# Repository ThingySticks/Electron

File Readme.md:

Electron Prototyping PCB.
=======================

Prototype board for Particle Electron.

See individual versions for PCB specifics.

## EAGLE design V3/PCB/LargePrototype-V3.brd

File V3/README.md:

Electron Prototype PCB.

Designed to fit Takachi WP11-15-4C case (150 x 110 x 40mm)

Farnell: 2472097

[Available on Tindie](https://www.tindie.com/products/ThingySticks/photonelectron-prototyping-pcb-for-ip67-enclosure/)

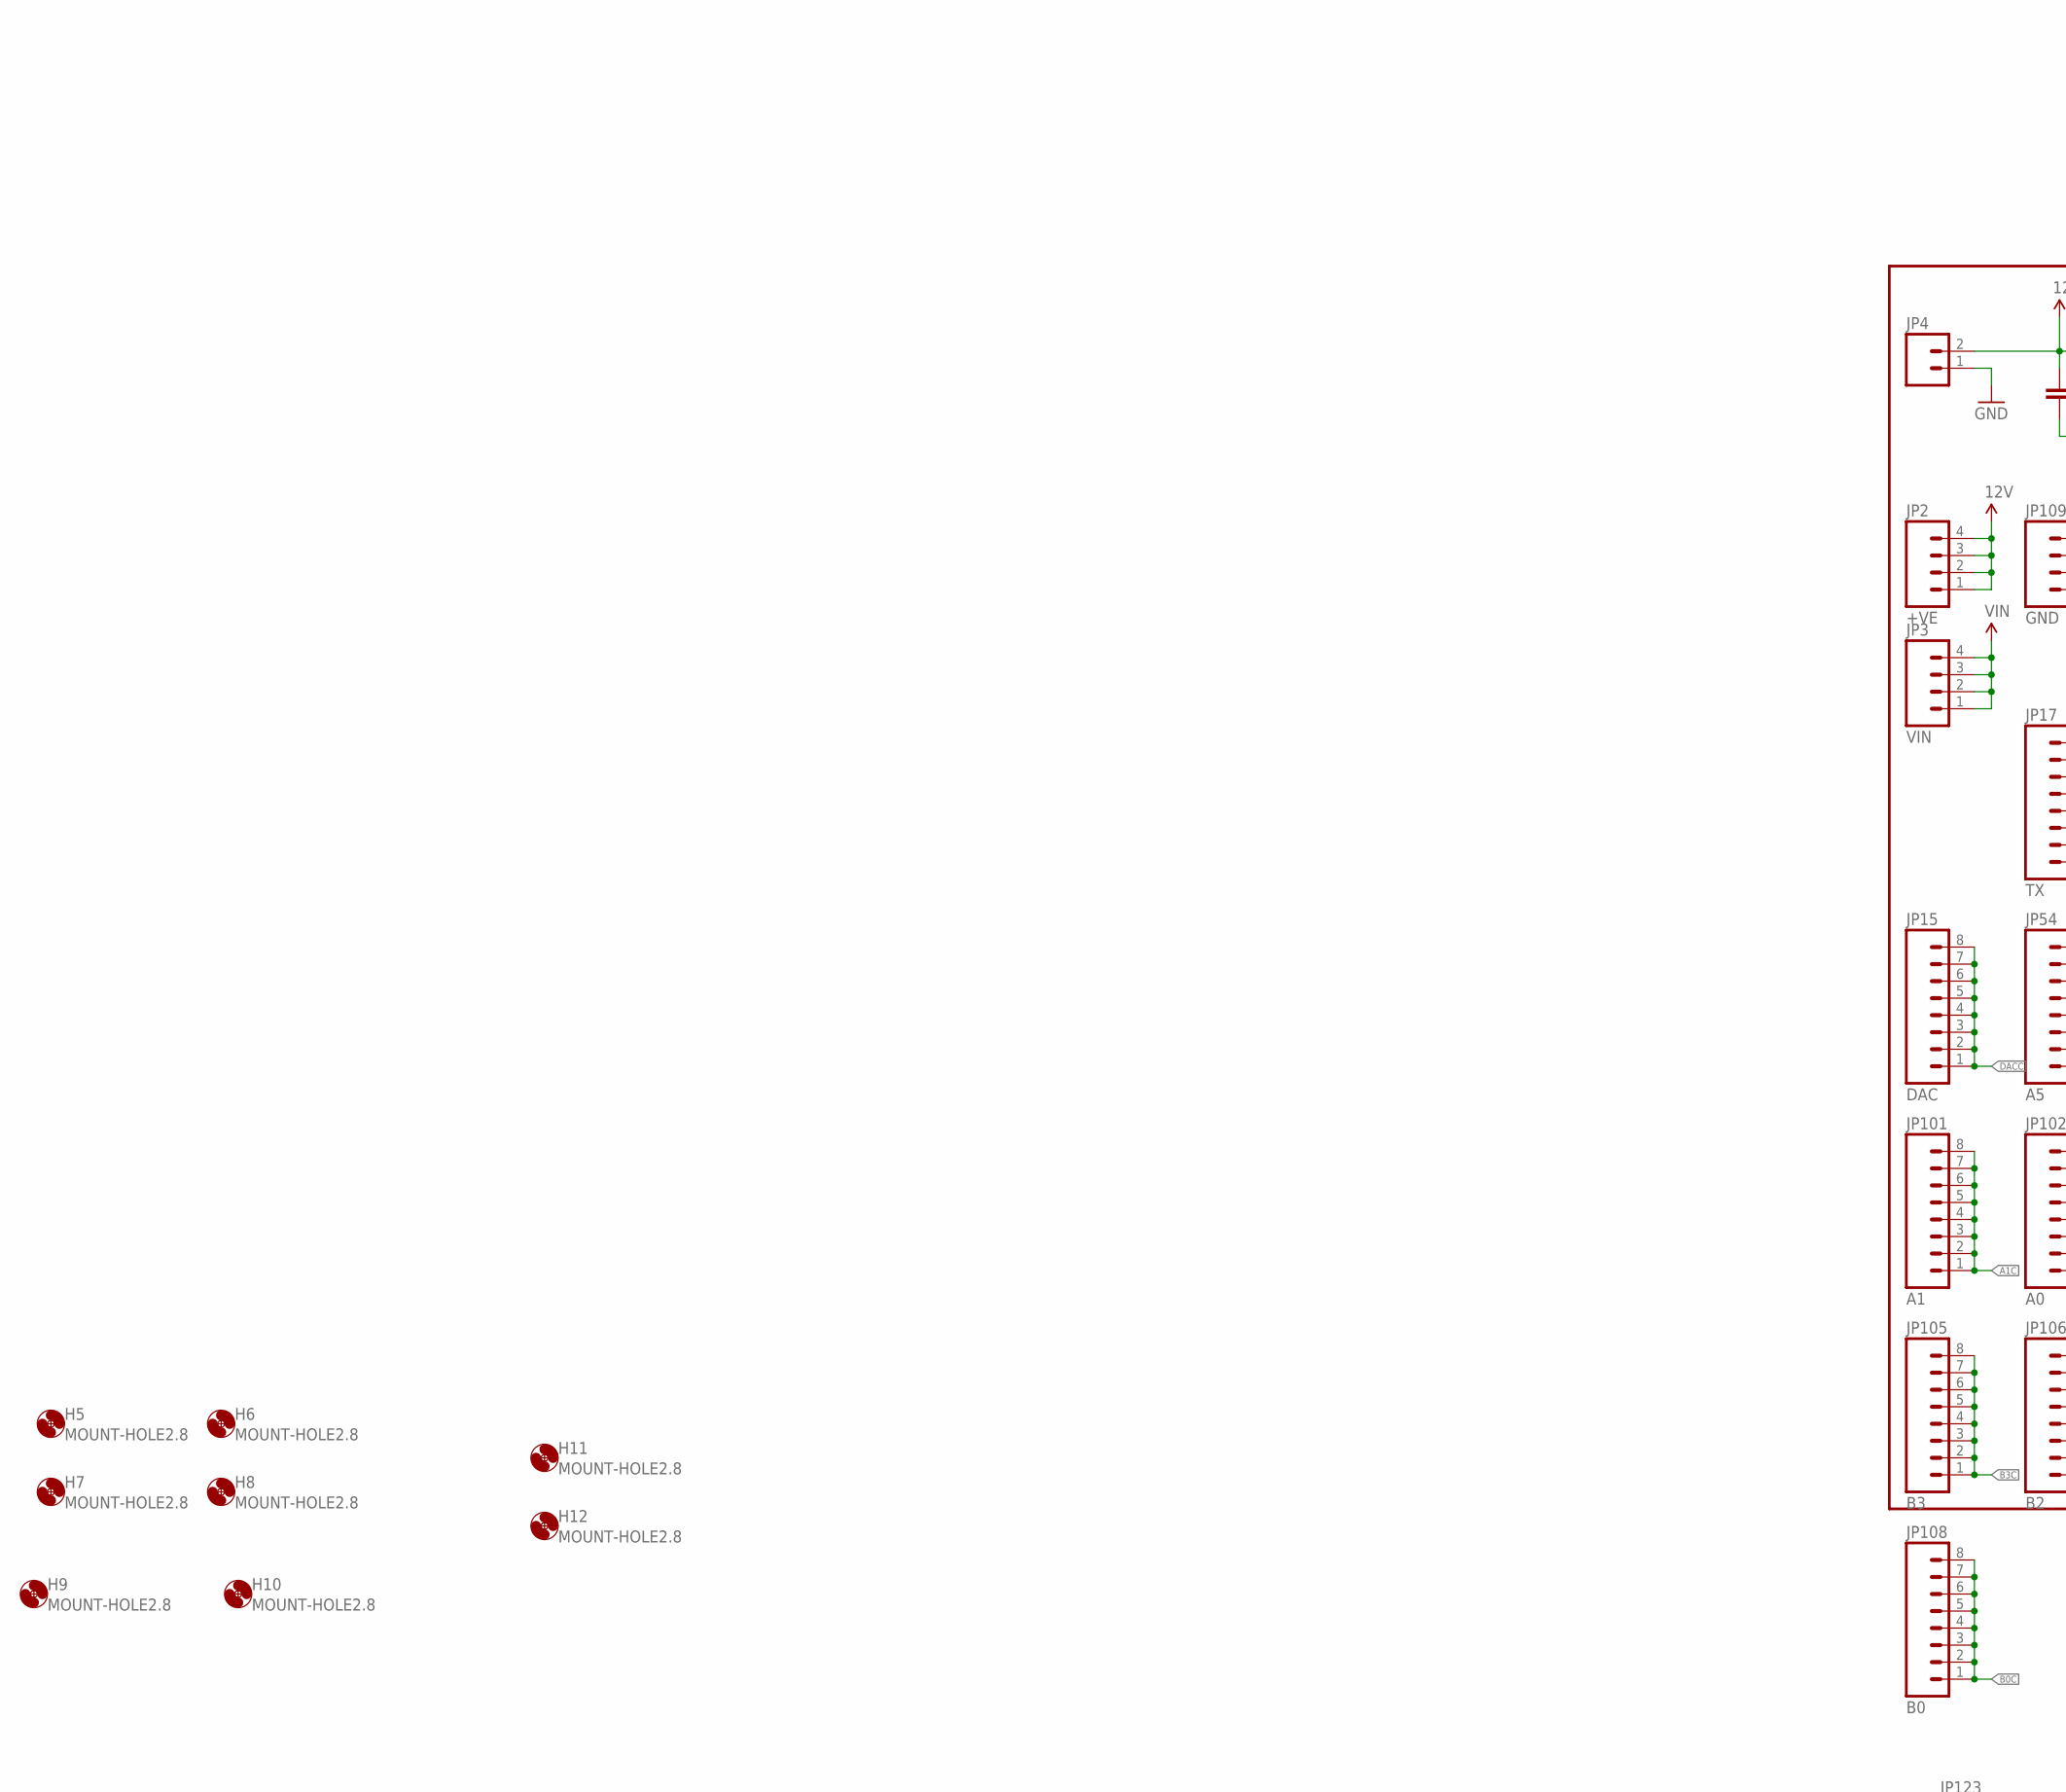
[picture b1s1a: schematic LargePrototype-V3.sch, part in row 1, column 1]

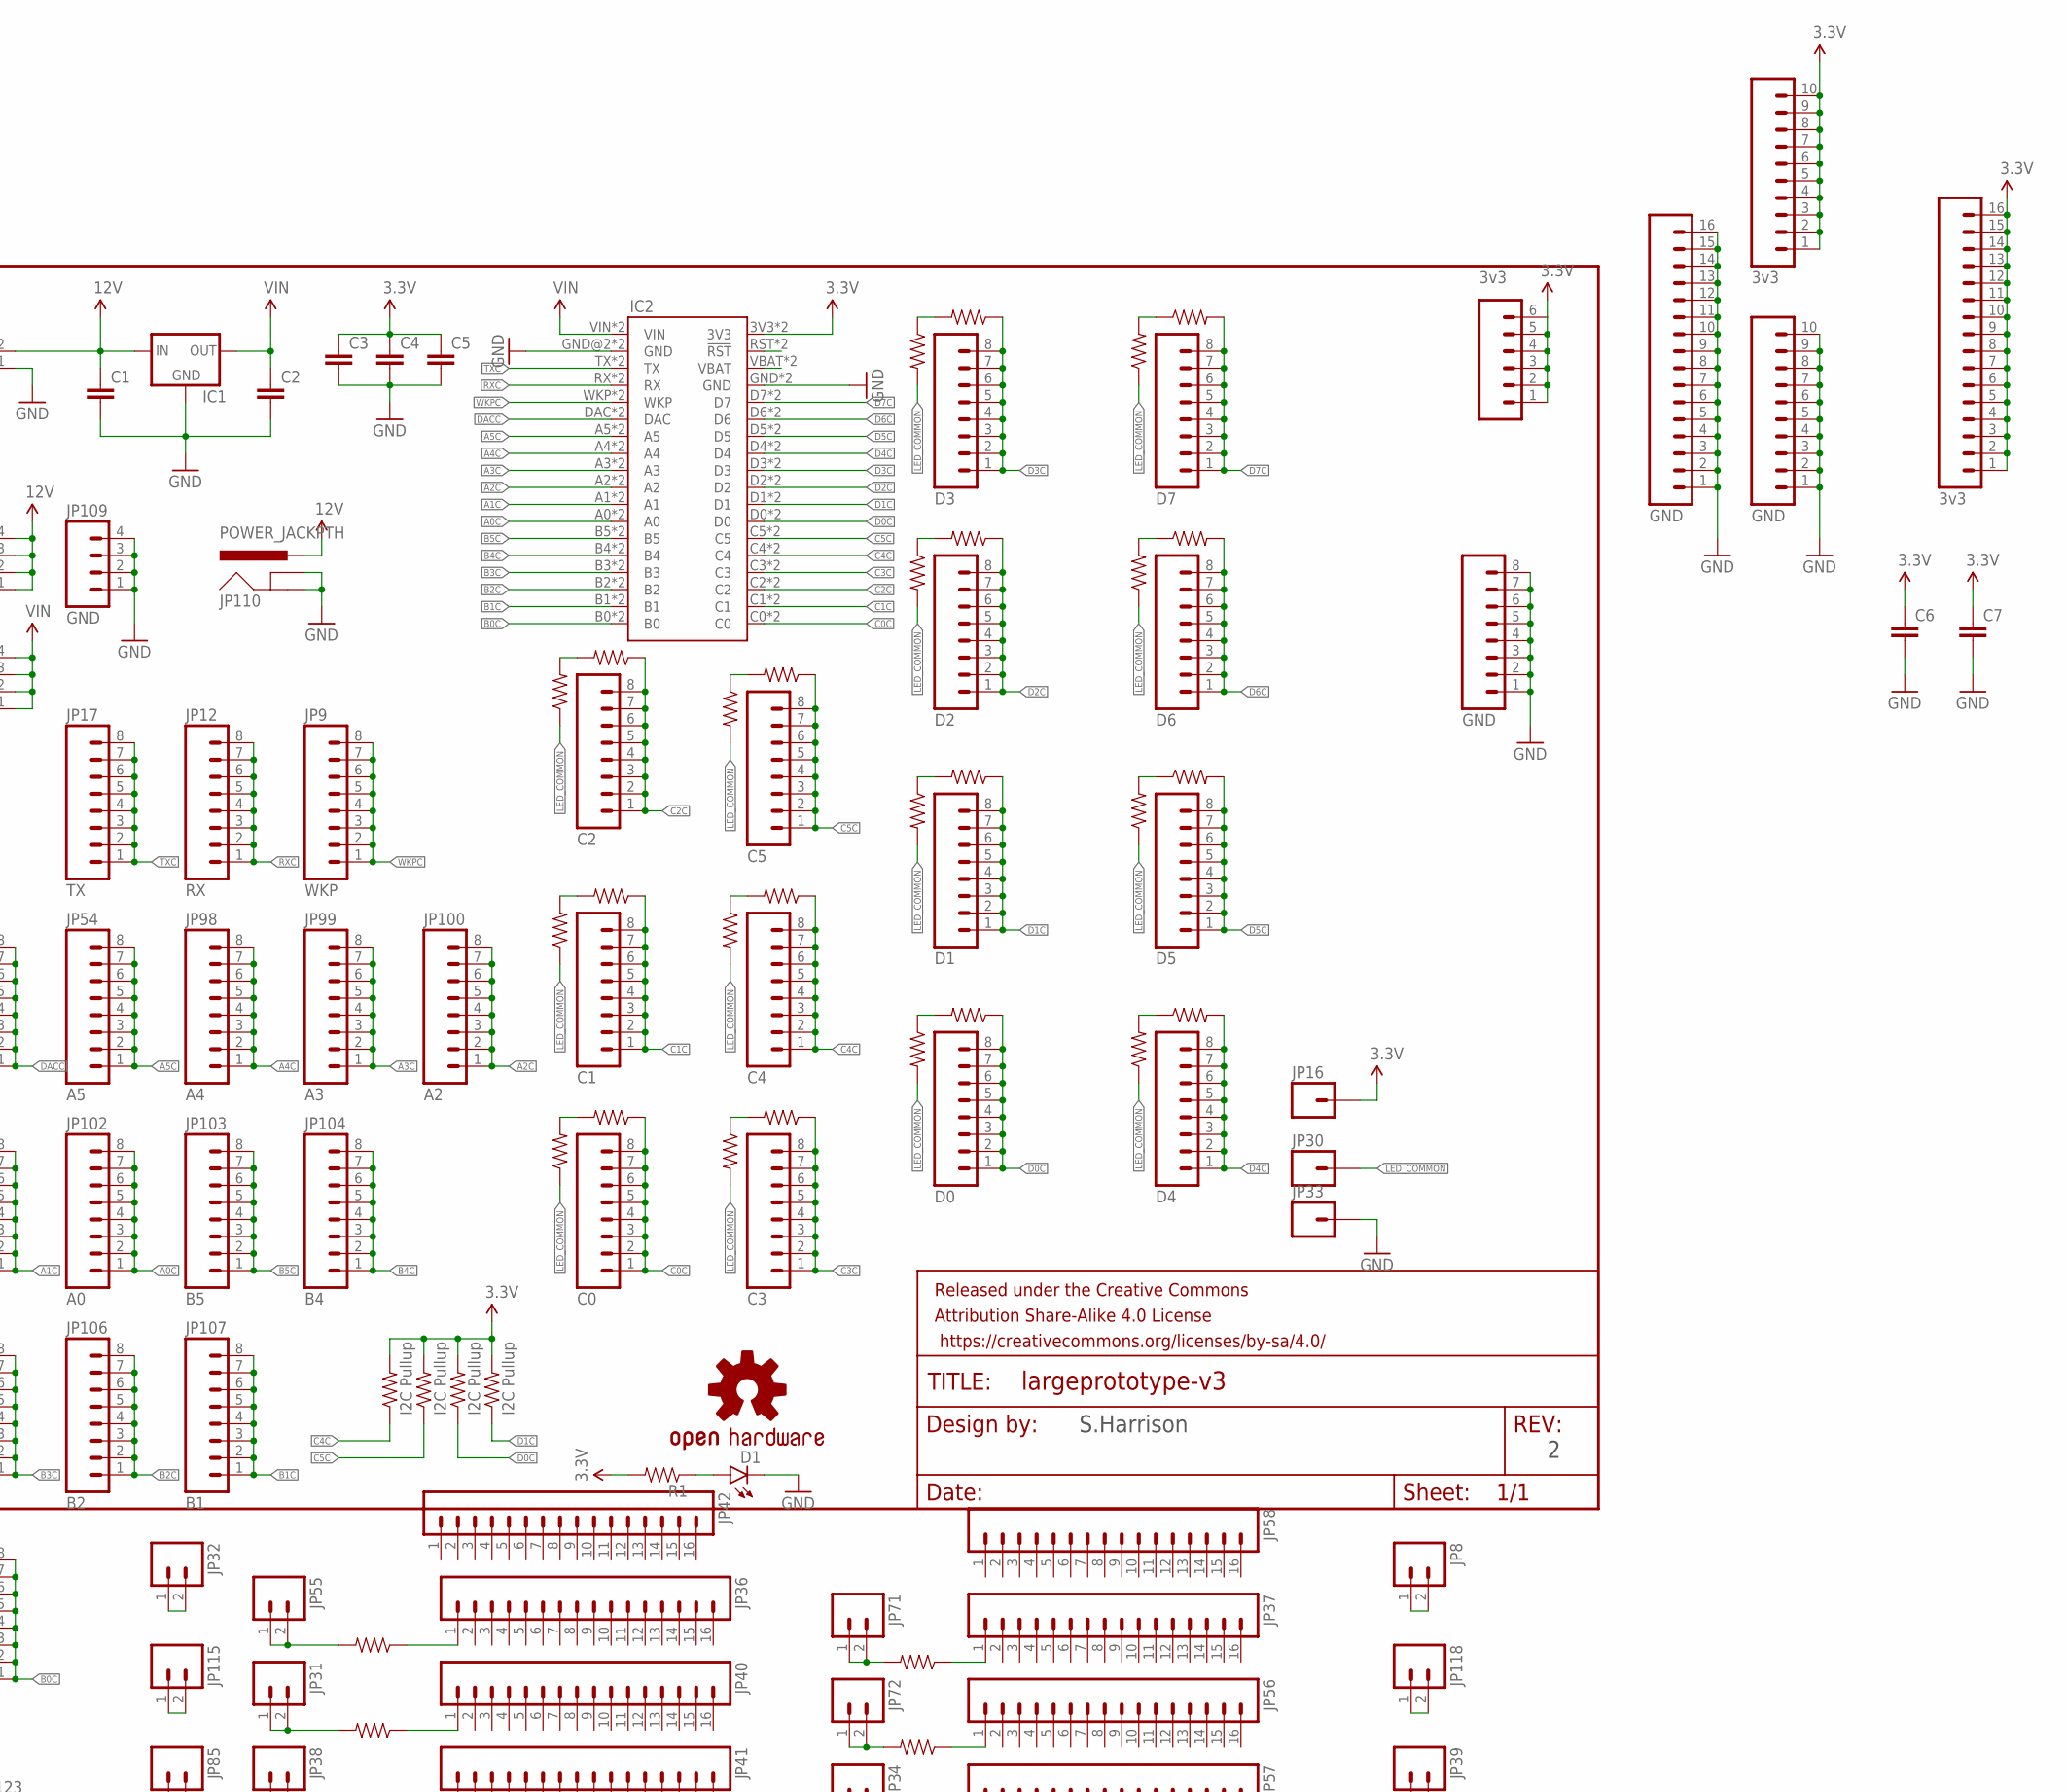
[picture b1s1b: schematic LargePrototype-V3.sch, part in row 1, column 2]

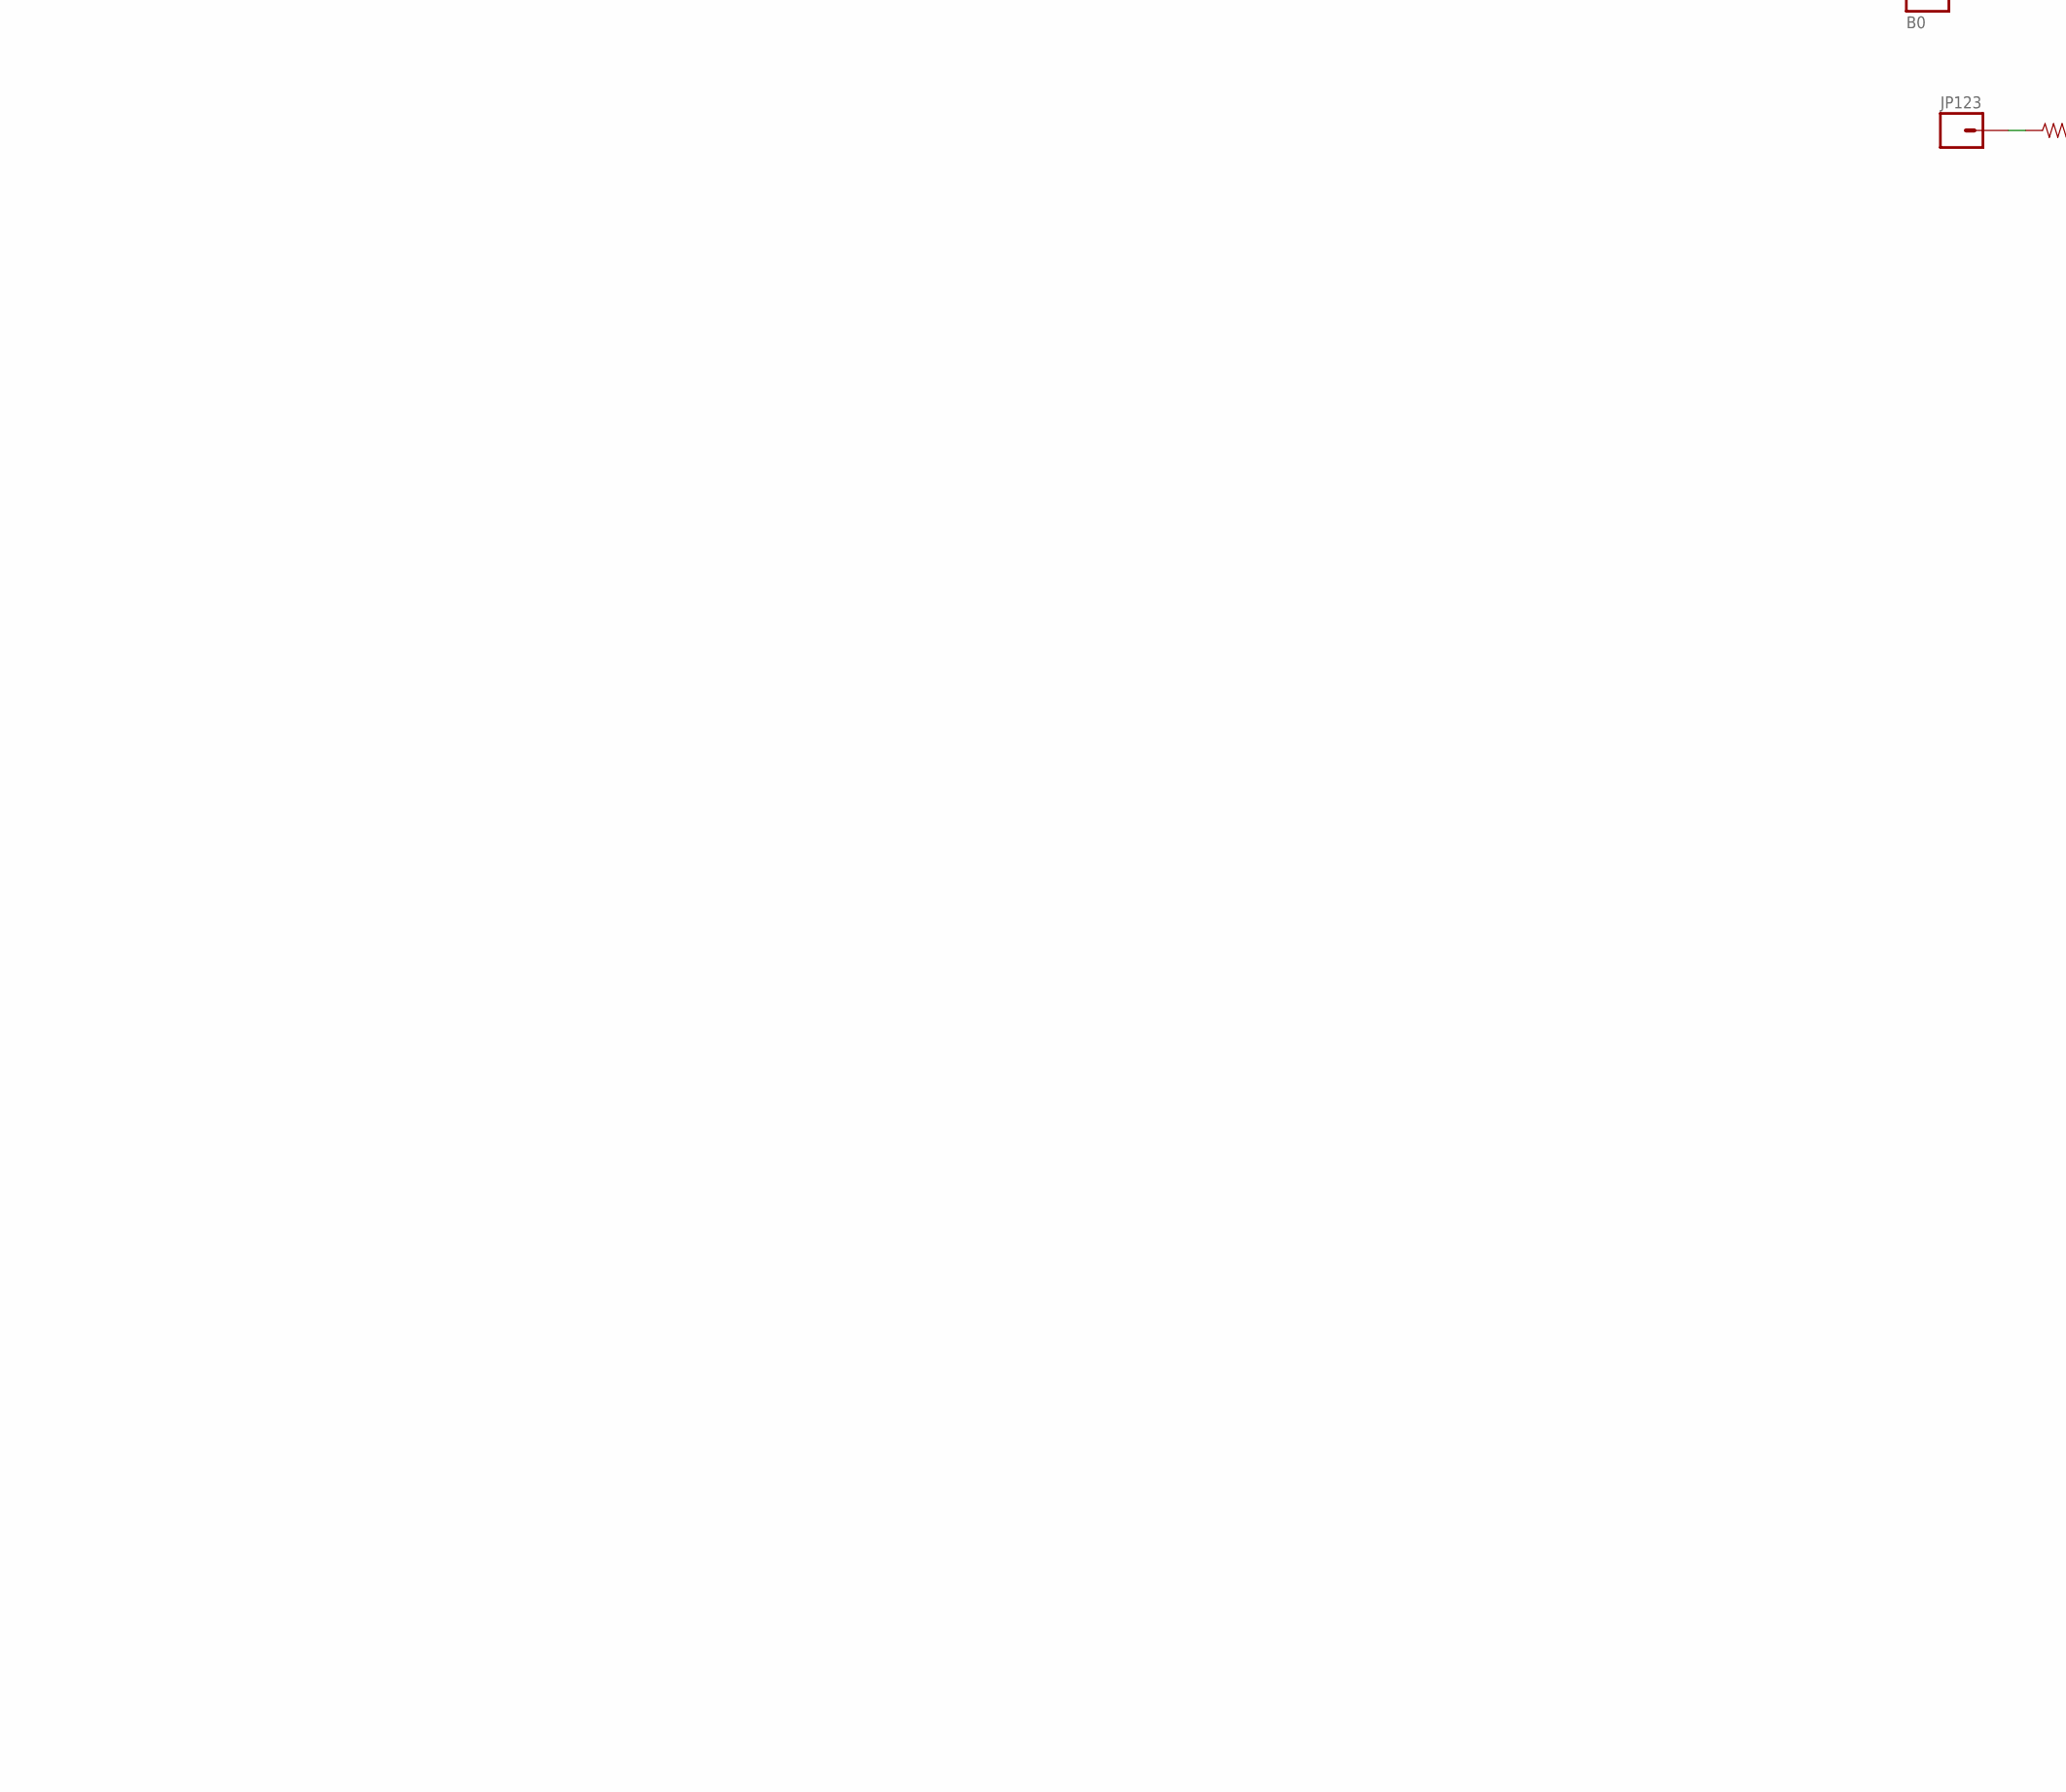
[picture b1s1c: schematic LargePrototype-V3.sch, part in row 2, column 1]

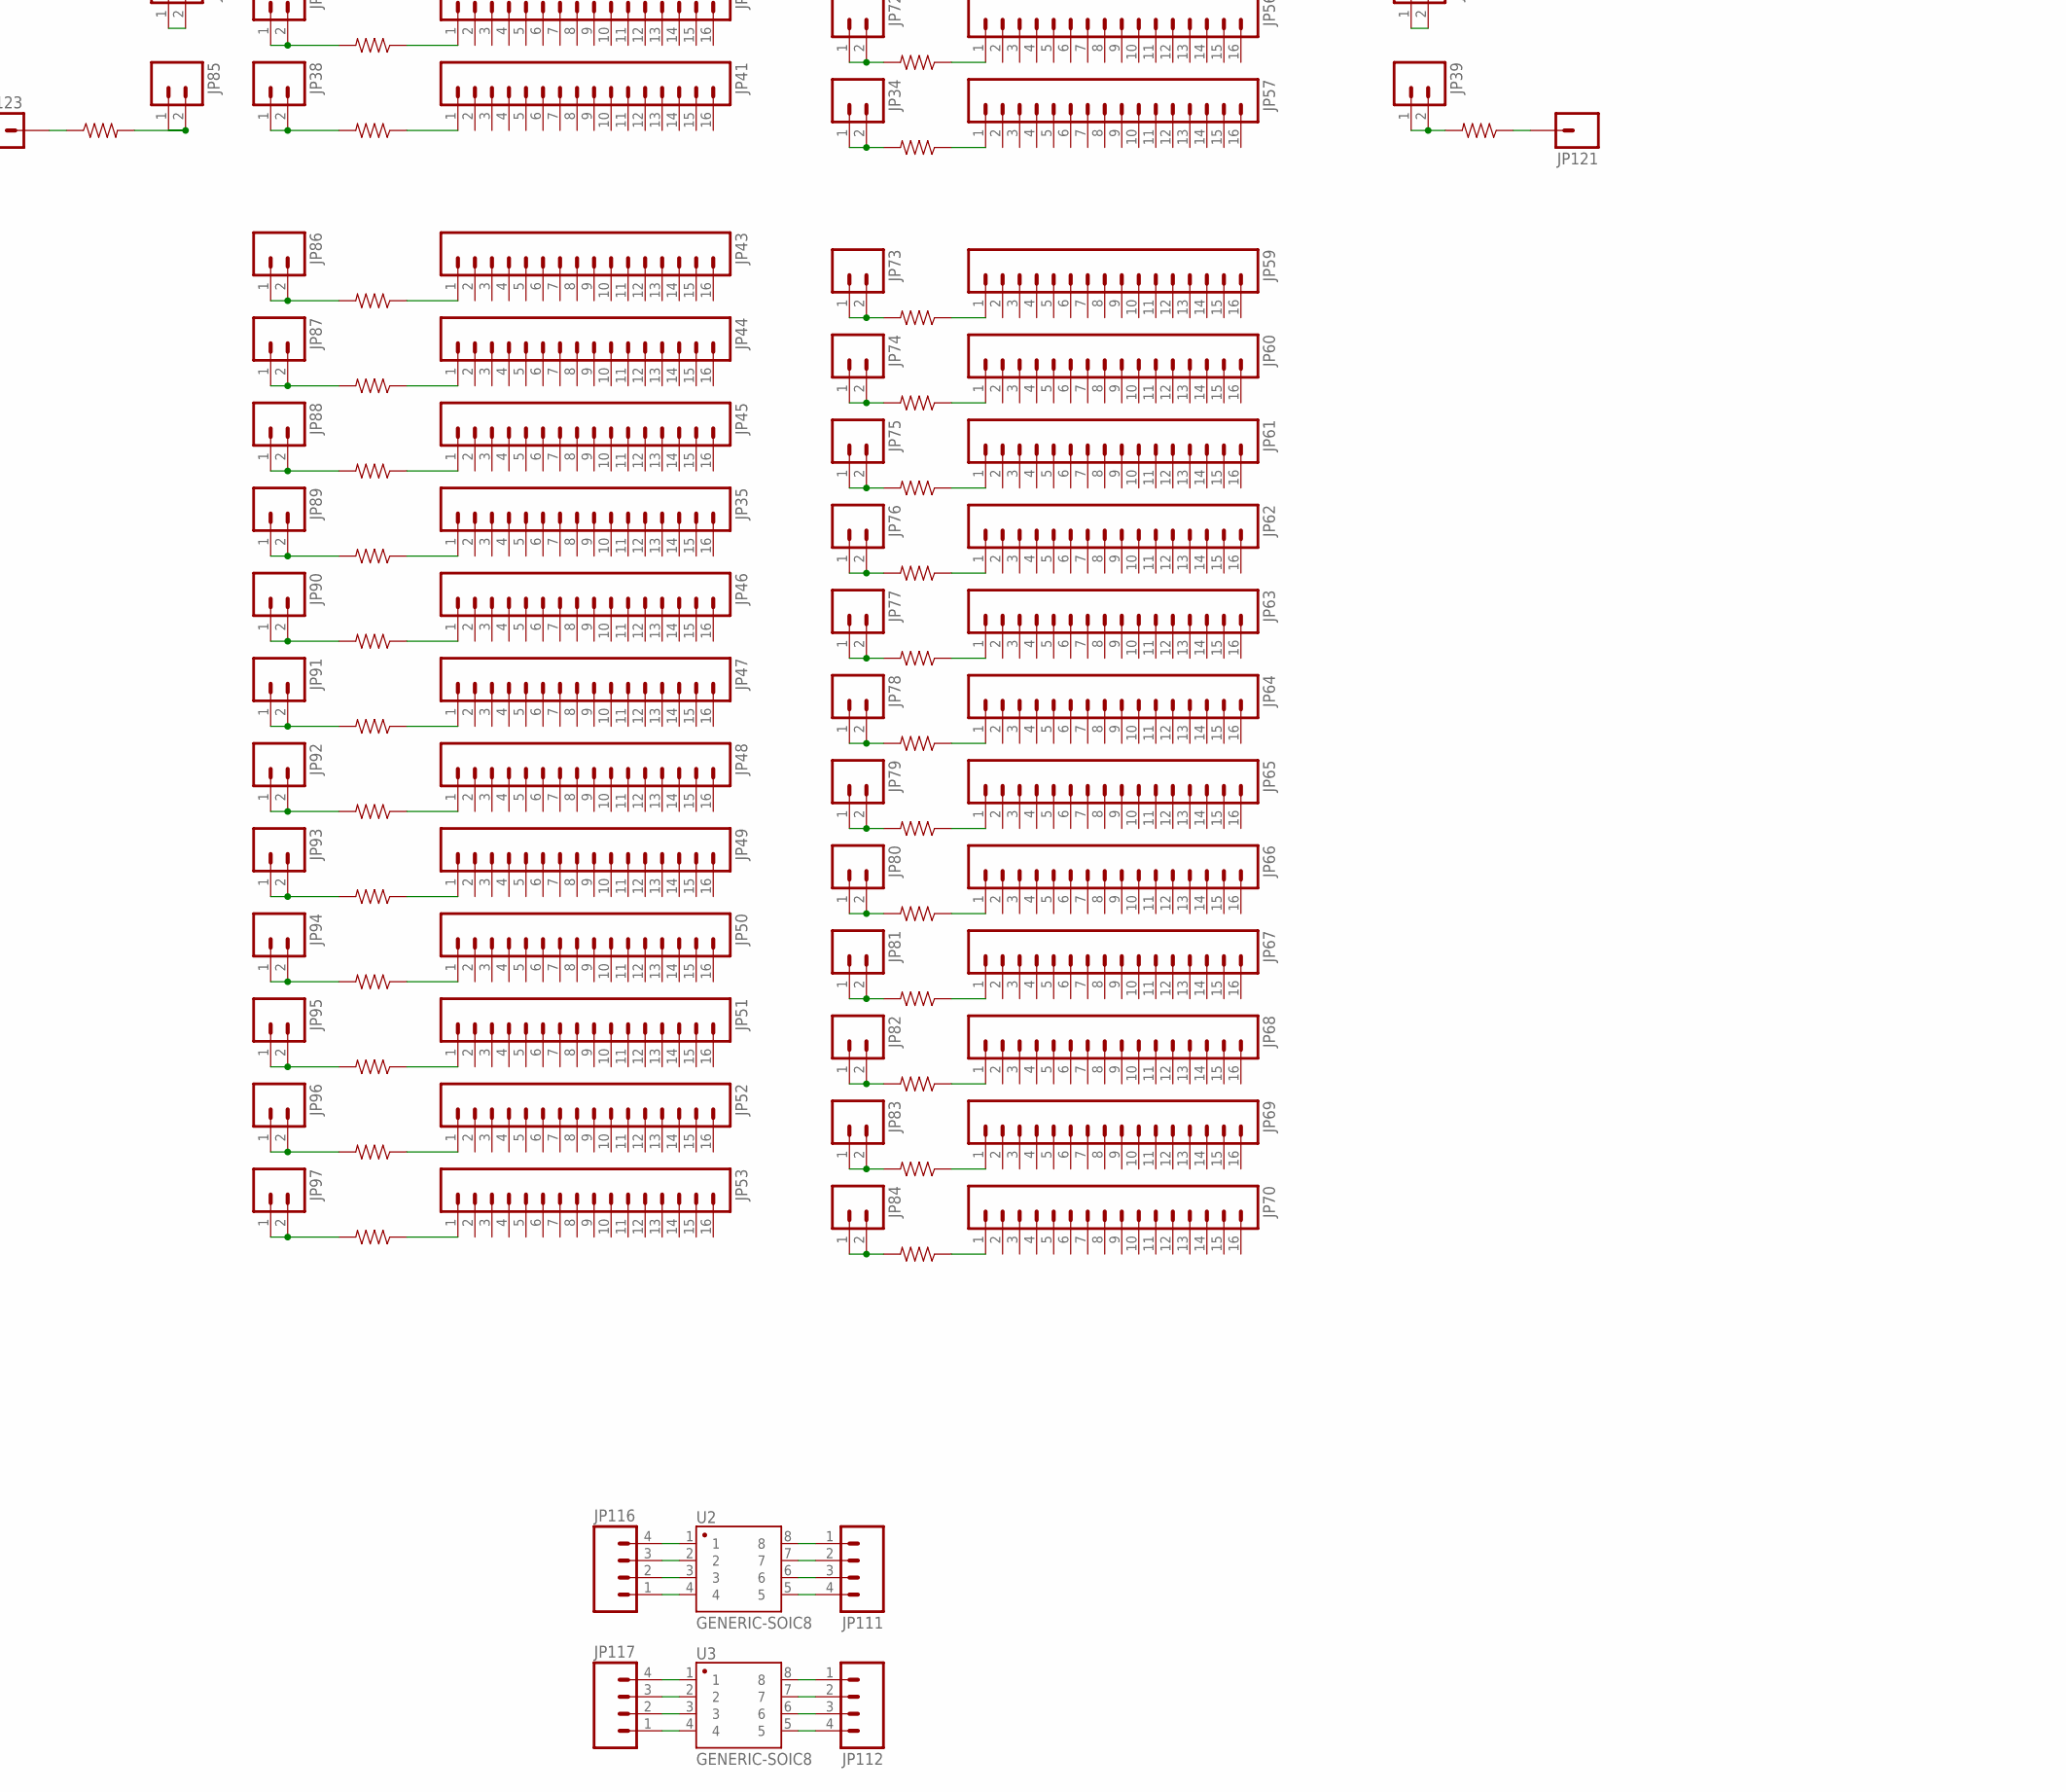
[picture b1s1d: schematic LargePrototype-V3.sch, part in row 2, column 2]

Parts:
C1, C2, C3, C4, C5, C6, C7: 1UF-25V-10%(0805)"; 0805-CAP
D1: LED1206-BOTTOM; LED-1206-BOTTOM
FRAME1: FRAME-LETTER; CREATIVE_COMMONS
H5, H6, H7, H8, H9, H10, H11, H12: MOUNT-HOLE2.8; 2,8
IC1: 78XXS
IC2: ELECTRONDUALNAMED; ELECTRON_SIMPLE_SILK_NAMES_DUAL
JP1: D7; 1X08_ROUND
JP2: +VE; 1X04
JP3: VIN; 1X04
JP4: M025MM; SCREWTERMINAL-5MM-2
JP5: 3v3; 1X10
JP6: 3v3; 1X06
JP7: D6; 1X08_ROUND
JP8, JP31, JP32, JP34, JP38, JP39, JP55, JP71, JP72, JP73, JP74, JP75, JP76, JP77, JP78, JP79, JP80, JP81, JP82, JP83, JP84, JP85, JP86, JP87, JP88, JP89, JP90, JP91, JP92, JP93, JP94, JP95, JP96, JP97, JP115, JP118: M02PTH; 1X02
JP9: WKP; 1X08_ROUND
JP10: D5; 1X08_ROUND
JP11: GND; 1X10
JP12: RX; 1X08_ROUND
JP13: 3v3; 1X16
JP14: GND; 1X16
JP15: DAC; 1X08_ROUND
JP16, JP30, JP33: M01PTH; 1X01
JP17: TX; 1X08_ROUND
JP18: D4; 1X08_ROUND
JP19: D3; 1X08_ROUND
JP20: D2; 1X08_ROUND
JP21: D1; 1X08_ROUND
JP22: D0; 1X08_ROUND
JP23: GND; 1X08_ROUND
JP24: C5; 1X08_ROUND
JP25: C4; 1X08_ROUND
JP26: C3; 1X08_ROUND
JP27: C2; 1X08_ROUND
JP28: C1; 1X08_ROUND
JP29: C0; 1X08_ROUND
JP35, JP36, JP37, JP40, JP41, JP42, JP43, JP44, JP45, JP46, JP47, JP48, JP49, JP50, JP51, JP52, JP53, JP56, JP57, JP58, JP59, JP60, JP61, JP62, JP63, JP64, JP65, JP66, JP67, JP68, JP69, JP70: M161X16_NO_SILK; 1X16_NO_SILK
JP54: A5; 1X08_ROUND
JP98: A4; 1X08_ROUND
JP99: A3; 1X08_ROUND
JP100: A2; 1X08_ROUND
JP101: A1; 1X08_ROUND
JP102: A0; 1X08_ROUND
JP103: B5; 1X08_ROUND
JP104: B4; 1X08_ROUND
JP105: B3; 1X08_ROUND
JP106: B2; 1X08_ROUND
JP107: B1; 1X08_ROUND
JP108: B0; 1X08_ROUND
JP109: GND; 1X04
JP110: POWER_JACKPTH; POWER_JACK_PTH
JP111, JP112, JP116, JP117: M04NO_SILK_ALL_ROUND; 1X04_NO_SILK_ALL_ROUND
JP121, JP123: M01NOSILK-KIT; 1X01NS-KIT
LOGO3: OSHW-LOGOM; OSHW-LOGO-M
R1, R2, R3, R4, R5, R6, R7, R8, R9, R10, R11, R12, R13, R14, R15, R16, R17, R18, R19, R20, R21, R22, R23, R24, R25, R26, R27, R28, R29, R30, R31, R32, R33, R34, R35, R36, R37, R38, R39, R40, R41, R42, R43, R44, R45, R46, R47, R48, R49, R50, R51, R52, R53, R54, R55, R56, R57, R58, R59, R60, R61: RESISTOR1206; 1206
R62, R63, R64, R65: I2C Pullup; 1206
U2, U3: GENERIC-SOIC8; SO08-UNIVERSAL

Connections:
3.3V: C3.1, C4.1, C5.1, C6.1, C7.1, IC2.3V3, IC2.3V3_1 (3V3), JP5.1, JP5.2, JP5.3, JP5.4, JP5.5, JP5.6, JP5.7, JP5.8, JP5.9, JP5.10, JP6.1, JP6.2, JP6.3, JP6.4, JP6.5, JP6.6, JP13.1, JP13.2, JP13.3, JP13.4, JP13.5, JP13.6, JP13.7, JP13.8, JP13.9, JP13.10, JP13.11, JP13.12, JP13.13, JP13.14, JP13.15, JP13.16, JP16.1, R1.2, R62.2, R63.2, R64.2, R65.2
12V: C1.1, IC1.IN, JP2.1, JP2.2, JP2.3, JP2.4, JP4.2, JP110.PWR
A0C: IC2.A0, IC2.A0_1 (A0), JP102.1, JP102.2, JP102.3, JP102.4, JP102.5, JP102.6, JP102.7, JP102.8
A1C: IC2.A1, IC2.A1_1 (A1), JP101.1, JP101.2, JP101.3, JP101.4, JP101.5, JP101.6, JP101.7, JP101.8
A2C: IC2.A2, IC2.A2_1 (A2), JP100.1, JP100.2, JP100.3, JP100.4, JP100.5, JP100.6, JP100.7, JP100.8
A3C: IC2.A3, IC2.A3_1 (A3), JP99.1, JP99.2, JP99.3, JP99.4, JP99.5, JP99.6, JP99.7, JP99.8
A4C: IC2.A4, IC2.A4_1 (A4), JP98.1, JP98.2, JP98.3, JP98.4, JP98.5, JP98.6, JP98.7, JP98.8
A5C: IC2.A5, IC2.A5_1 (A5), JP54.1, JP54.2, JP54.3, JP54.4, JP54.5, JP54.6, JP54.7, JP54.8
B0C: IC2.B0, IC2.B0_1 (B0), JP108.1, JP108.2, JP108.3, JP108.4, JP108.5, JP108.6, JP108.7, JP108.8
B1C: IC2.B1, IC2.B1_1 (B1), JP107.1, JP107.2, JP107.3, JP107.4, JP107.5, JP107.6, JP107.7, JP107.8
B2C: IC2.B2, IC2.B2_1 (B2), JP106.1, JP106.2, JP106.3, JP106.4, JP106.5, JP106.6, JP106.7, JP106.8
B3C: IC2.B3, IC2.B3_1 (B3), JP105.1, JP105.2, JP105.3, JP105.4, JP105.5, JP105.6, JP105.7, JP105.8
B4C: IC2.B4, IC2.B4_1 (B4), JP104.1, JP104.2, JP104.3, JP104.4, JP104.5, JP104.6, JP104.7, JP104.8
B5C: IC2.B5, IC2.B5_1 (B5), JP103.1, JP103.2, JP103.3, JP103.4, JP103.5, JP103.6, JP103.7, JP103.8
C0C: IC2.C0, IC2.C0_1 (C0), JP29.1, JP29.2, JP29.3, JP29.4, JP29.5, JP29.6, JP29.7, JP29.8, R28.1
C1C: IC2.C1, IC2.C1_1 (C1), JP28.1, JP28.2, JP28.3, JP28.4, JP28.5, JP28.6, JP28.7, JP28.8, R26.1
C2C: IC2.C2, IC2.C2_1 (C2), JP27.1, JP27.2, JP27.3, JP27.4, JP27.5, JP27.6, JP27.7, JP27.8, R24.1
C3C: IC2.C3, IC2.C3_1 (C3), JP26.1, JP26.2, JP26.3, JP26.4, JP26.5, JP26.6, JP26.7, JP26.8, R22.1
C4C: IC2.C4, IC2.C4_1 (C4), JP25.1, JP25.2, JP25.3, JP25.4, JP25.5, JP25.6, JP25.7, JP25.8, R20.1, R65.1
C5C: IC2.C5, IC2.C5_1 (C5), JP24.1, JP24.2, JP24.3, JP24.4, JP24.5, JP24.6, JP24.7, JP24.8, R18.1, R64.1
D0C: IC2.D0, IC2.D0_1 (D0), JP22.1, JP22.2, JP22.3, JP22.4, JP22.5, JP22.6, JP22.7, JP22.8, R16.1, R62.1
D1C: IC2.D1, IC2.D1_1 (D1), JP21.1, JP21.2, JP21.3, JP21.4, JP21.5, JP21.6, JP21.7, JP21.8, R14.1, R63.1
D2C: IC2.D2, IC2.D2_1 (D2), JP20.1, JP20.2, JP20.3, JP20.4, JP20.5, JP20.6, JP20.7, JP20.8, R12.1
D3C: IC2.D3, IC2.D3_1 (D3), JP19.1, JP19.2, JP19.3, JP19.4, JP19.5, JP19.6, JP19.7, JP19.8, R10.1
D4C: IC2.D4, IC2.D4_1 (D4), JP18.1, JP18.2, JP18.3, JP18.4, JP18.5, JP18.6, JP18.7, JP18.8, R8.2
D5C: IC2.D5, IC2.D5_1 (D5), JP10.1, JP10.2, JP10.3, JP10.4, JP10.5, JP10.6, JP10.7, JP10.8, R6.2
D6C: IC2.D6, IC2.D6_1 (D6), JP7.1, JP7.2, JP7.3, JP7.4, JP7.5, JP7.6, JP7.7, JP7.8, R4.2
D7C: IC2.D7, IC2.D7_1 (D7), JP1.1, JP1.2, JP1.3, JP1.4, JP1.5, JP1.6, JP1.7, JP1.8, R3.2
DACC: IC2.DAC, IC2.DAC_1 (DAC), JP15.1, JP15.2, JP15.3, JP15.4, JP15.5, JP15.6, JP15.7, JP15.8
GND: C1.2, C2.2, C3.2, C4.2, C5.2, C6.2, C7.2, D1.C, IC1.GND, IC2.GND, IC2.GND@2 (GND), IC2.GND_1 (GND), IC2.GND_1B (GND), JP4.1, JP11.1, JP11.2, JP11.3, JP11.4, JP11.5, JP11.6, JP11.7, JP11.8, JP11.9, JP11.10, JP14.1, JP14.2, JP14.3, JP14.4, JP14.5, JP14.6, JP14.7, JP14.8, JP14.9, JP14.10, JP14.11, JP14.12, JP14.13, JP14.14, JP14.15, JP14.16, JP23.1, JP23.2, JP23.3, JP23.4, JP23.5, JP23.6, JP23.7, JP23.8, JP33.1, JP109.1, JP109.2, JP109.3, JP109.4, JP110.GND, JP110.GNDBREAK
LED_COMMON: JP30.1, R2.1, R5.1, R7.1, R9.1, R11.2, R13.2, R15.2, R17.2, R19.2, R21.2, R23.2, R25.1, R27.1, R29.1
unnamed: D1.A, R1.1
unnamed: JP32.1, JP32.2
unnamed: JP115.1, JP115.2
unnamed: R4.1, R5.2
unnamed: R2.2, R3.1
unnamed: R10.2, R11.1
unnamed: JP8.1, JP8.2
unnamed: JP118.1, JP118.2
unnamed: JP123.1, R33.1
unnamed: R8.1, R9.2
unnamed: R6.1, R7.2
unnamed: JP121.1, R49.1
unnamed: R12.2, R13.1
unnamed: R14.2, R15.1
unnamed: R16.2, R17.1
unnamed: JP116.4, U2.1
unnamed: R18.2, R19.1
unnamed: JP116.3, U2.2
unnamed: R20.2, R21.1
unnamed: JP116.2, U2.3
unnamed: R22.2, R23.1
unnamed: R28.2, R29.2
unnamed: JP71.1, JP71.2, R46.2
unnamed: JP116.1, U2.4
unnamed: R26.2, R27.2
unnamed: JP117.4, U3.1
unnamed: R24.2, R25.2
unnamed: JP117.3, U3.2
unnamed: JP72.1, JP72.2, R47.2
unnamed: JP34.1, JP34.2, R48.2
unnamed: JP39.1, JP39.2, R49.2
unnamed: JP73.1, JP73.2, R50.2
unnamed: JP74.1, JP74.2, R51.2
unnamed: JP75.1, JP75.2, R52.2
unnamed: JP76.1, JP76.2, R53.2
unnamed: JP77.1, JP77.2, R54.2
unnamed: JP78.1, JP78.2, R55.2
unnamed: JP79.1, JP79.2, R56.2
unnamed: JP80.1, JP80.2, R57.2
unnamed: JP81.1, JP81.2, R58.2
unnamed: JP82.1, JP82.2, R59.2
unnamed: JP83.1, JP83.2, R60.2
unnamed: JP84.1, JP84.2, R61.2
unnamed: JP70.1, R61.1
unnamed: JP69.1, R60.1
unnamed: JP68.1, R59.1
unnamed: JP67.1, R58.1
unnamed: JP66.1, R57.1
unnamed: JP65.1, R56.1
unnamed: JP64.1, R55.1
unnamed: JP63.1, R54.1
unnamed: JP62.1, R53.1
unnamed: JP61.1, R52.1
unnamed: JP60.1, R51.1
unnamed: JP59.1, R50.1
unnamed: JP57.1, R48.1
unnamed: JP56.1, R47.1
unnamed: JP37.1, R46.1
unnamed: JP97.1, JP97.2, R45.2
unnamed: JP96.1, JP96.2, R44.2
unnamed: JP95.1, JP95.2, R43.2
unnamed: JP94.1, JP94.2, R42.2
unnamed: JP93.1, JP93.2, R41.2
unnamed: JP92.1, JP92.2, R40.2
unnamed: JP91.1, JP91.2, R39.2
unnamed: JP90.1, JP90.2, R38.2
unnamed: JP89.1, JP89.2, R37.2
unnamed: JP88.1, JP88.2, R36.2
unnamed: JP87.1, JP87.2, R35.2
unnamed: JP86.1, JP86.2, R34.2
unnamed: JP85.1, JP85.2, R33.2
unnamed: JP38.1, JP38.2, R32.2
unnamed: JP55.1, JP55.2, R30.2
unnamed: JP36.1, R30.1
unnamed: JP40.1, R31.1
unnamed: JP41.1, R32.1
unnamed: JP43.1, R34.1
unnamed: JP44.1, R35.1
unnamed: JP45.1, R36.1
unnamed: JP35.1, R37.1
unnamed: JP46.1, R38.1
unnamed: JP47.1, R39.1
unnamed: JP48.1, R40.1
unnamed: JP49.1, R41.1
unnamed: JP50.1, R42.1
unnamed: JP51.1, R43.1
unnamed: JP52.1, R44.1
unnamed: JP53.1, R45.1
unnamed: JP31.1, JP31.2, R31.2
unnamed: JP117.2, U3.3
unnamed: JP117.1, U3.4
unnamed: IC2.VBAT, IC2.VBATT_1 (VBAT)
unnamed: IC2.RST (!RST), IC2.RST_1 (!RST)
unnamed: JP112.4, U3.5
unnamed: JP112.3, U3.6
unnamed: JP112.2, U3.7
unnamed: JP112.1, U3.8
unnamed: JP111.4, U2.5
unnamed: JP111.3, U2.6
unnamed: JP111.2, U2.7
unnamed: JP111.1, U2.8
RXC: IC2.RX, IC2.RX_1 (RX), JP12.1, JP12.2, JP12.3, JP12.4, JP12.5, JP12.6, JP12.7, JP12.8
TXC: IC2.TX, IC2.TX_1 (TX), JP17.1, JP17.2, JP17.3, JP17.4, JP17.5, JP17.6, JP17.7, JP17.8
VIN: C2.1, IC1.OUT, IC2.VIN, IC2.VIN_1B (VIN), JP3.1, JP3.2, JP3.3, JP3.4
WKPC: IC2.WKP, IC2.WKP_1 (WKP), JP9.1, JP9.2, JP9.3, JP9.4, JP9.5, JP9.6, JP9.7, JP9.8

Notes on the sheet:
S.Harrison

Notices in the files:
parts and their libraries:
SparkFun-Connectors: Licensing: Creative Commons ShareAlike 4.0 International - https://creativecommons.org/licenses/by-sa/4.0
SparkFun-Aesthetics: Released under the Creative Commons Attribution Share-Alike 4.0 License
SparkFun-Aesthetics: https://creativecommons.org/licenses/by-sa/4.0
